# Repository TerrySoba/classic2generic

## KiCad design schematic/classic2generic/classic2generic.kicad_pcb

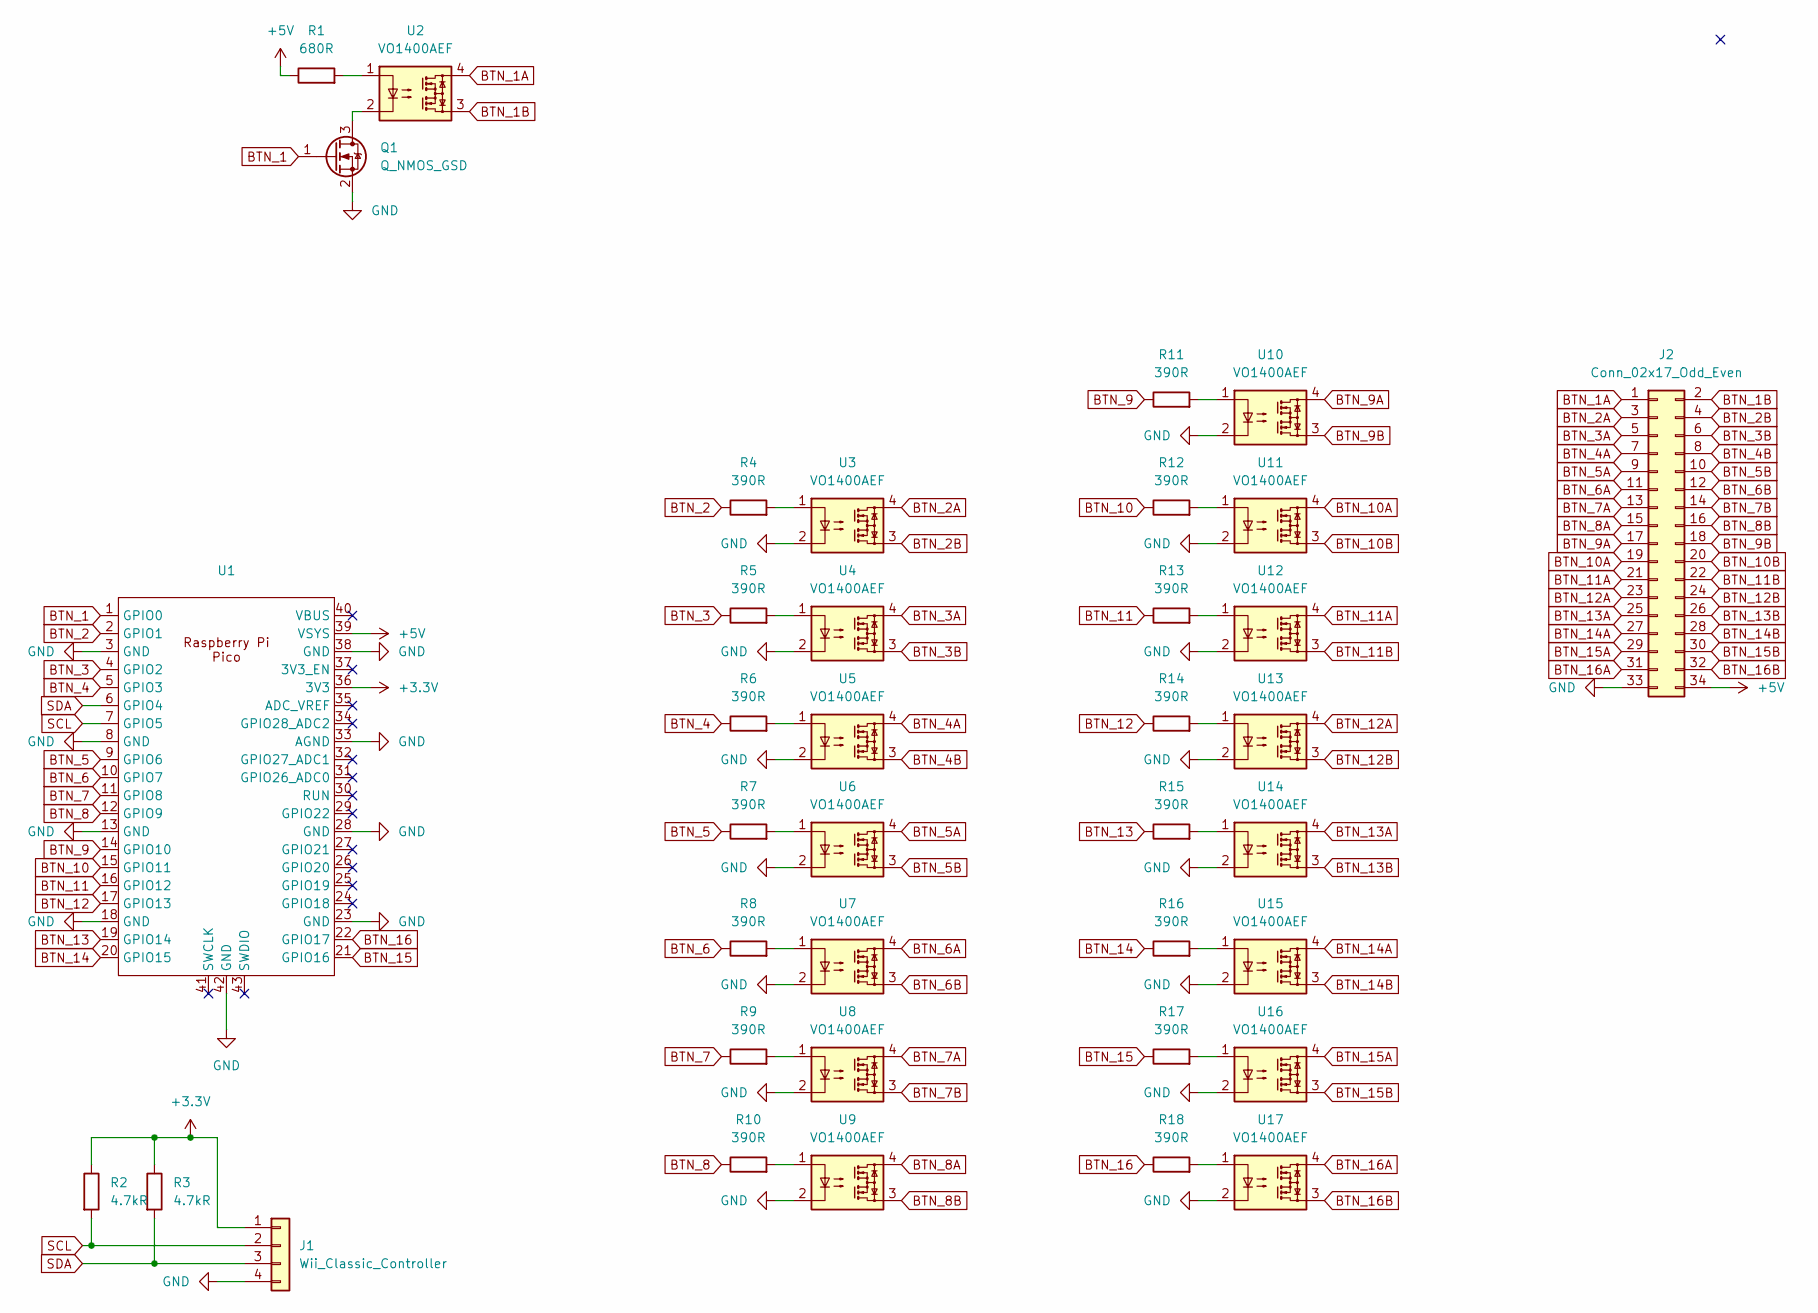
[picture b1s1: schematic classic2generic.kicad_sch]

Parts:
J1: Wii_Classic_Controller; Molex_KK-254_AE-6410-04A_1x04_P2.54mm_Vertical
J2: Conn_02x17_Odd_Even; IDC-Header_2x17_P2.54mm_Vertical
Q1: Q_NMOS_GSD
R1: 680R; R_0603_1608Metric_Pad0.98x0.95mm_HandSolder
R2, R3: 4.7kR; R_0805_2012Metric_Pad1.20x1.40mm_HandSolder
R4, R5, R6, R7, R8, R9, R10, R11, R12, R13, R14, R15, R16, R17, R18: 390R; R_0603_1608Metric_Pad0.98x0.95mm_HandSolder
U1: RPi_Pico_SMD_TH
U2, U3, U4, U5, U6, U7, U8, U9, U10, U11, U12, U13, U14, U15, U16, U17: VO1400AEF; SO-4_4.4x4.3mm_P2.54mm

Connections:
+3.3V: J1.1, R2.1, R3.1, U1.36 (3V3)
BTN_1A: J2.1, U2.4
BTN_1B: J2.2, U2.3
BTN_2: R4.1, U1.2 (GPIO1)
BTN_2A: J2.3, U3.4
BTN_2B: J2.4, U3.3
BTN_3: R5.1, U1.4 (GPIO2)
BTN_3A: J2.5, U4.4
BTN_3B: J2.6, U4.3
BTN_4: R6.1, U1.5 (GPIO3)
BTN_4A: J2.7, U5.4
BTN_4B: J2.8, U5.3
BTN_5: R7.1, U1.9 (GPIO6)
BTN_5A: J2.9, U6.4
BTN_5B: J2.10, U6.3
BTN_6: R8.1, U1.10 (GPIO7)
BTN_6A: J2.11, U7.4
BTN_6B: J2.12, U7.3
BTN_7: R9.1, U1.11 (GPIO8)
BTN_7A: J2.13, U8.4
BTN_7B: J2.14, U8.3
BTN_8: R10.1, U1.12 (GPIO9)
BTN_8A: J2.15, U9.4
BTN_8B: J2.16, U9.3
BTN_9: R11.1, U1.14 (GPIO10)
BTN_9A: J2.17, U10.4
BTN_9B: J2.18, U10.3
BTN_10: R12.1, U1.15 (GPIO11)
BTN_10A: J2.19, U11.4
BTN_10B: J2.20, U11.3
BTN_11: R13.1, U1.16 (GPIO12)
BTN_11A: J2.21, U12.4
BTN_11B: J2.22, U12.3
BTN_12: R14.1, U1.17 (GPIO13)
BTN_12A: J2.23, U13.4
BTN_12B: J2.24, U13.3
BTN_13: R15.1, U1.19 (GPIO14)
BTN_13A: J2.25, U14.4
BTN_13B: J2.26, U14.3
BTN_14: R16.1, U1.20 (GPIO15)
BTN_14A: J2.27, U15.4
BTN_14B: J2.28, U15.3
BTN_15: R17.1, U1.21 (GPIO16)
BTN_15A: J2.29, U16.4
BTN_15B: J2.30, U16.3
BTN_16: R18.1, U1.22 (GPIO17)
BTN_16A: J2.31, U17.4
BTN_16B: J2.32, U17.3
GND: J1.4, J2.33, Q1.2 (S), Q1.3 (D), U1.3 (GND), U1.8 (GND), U1.13 (GND), U1.18 (GND), U1.23 (GND), U1.28 (GND), U1.33 (AGND), U1.38 (GND), U1.42 (GND), U2.2, U3.2, U4.2, U5.2, U6.2, U7.2, U8.2, U9.2, U10.2, U11.2, U12.2, U13.2, U14.2, U15.2, U16.2, U17.2
unnamed: R1.2, U2.1
unnamed: R4.2, U3.1
unnamed: R5.2, U4.1
unnamed: R6.2, U5.1
unnamed: R7.2, U6.1
unnamed: R8.2, U7.1
unnamed: R9.2, U8.1
unnamed: R10.2, U9.1
unnamed: R11.2, U10.1
unnamed: R12.2, U11.1
unnamed: R13.2, U12.1
unnamed: R14.2, U13.1
unnamed: R15.2, U14.1
unnamed: R16.2, U15.1
unnamed: R17.2, U16.1
unnamed: R18.2, U17.1
SCL: J1.2, R2.2, U1.7 (GPIO5)
SDA: J1.3, R3.2, U1.6 (GPIO4)

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
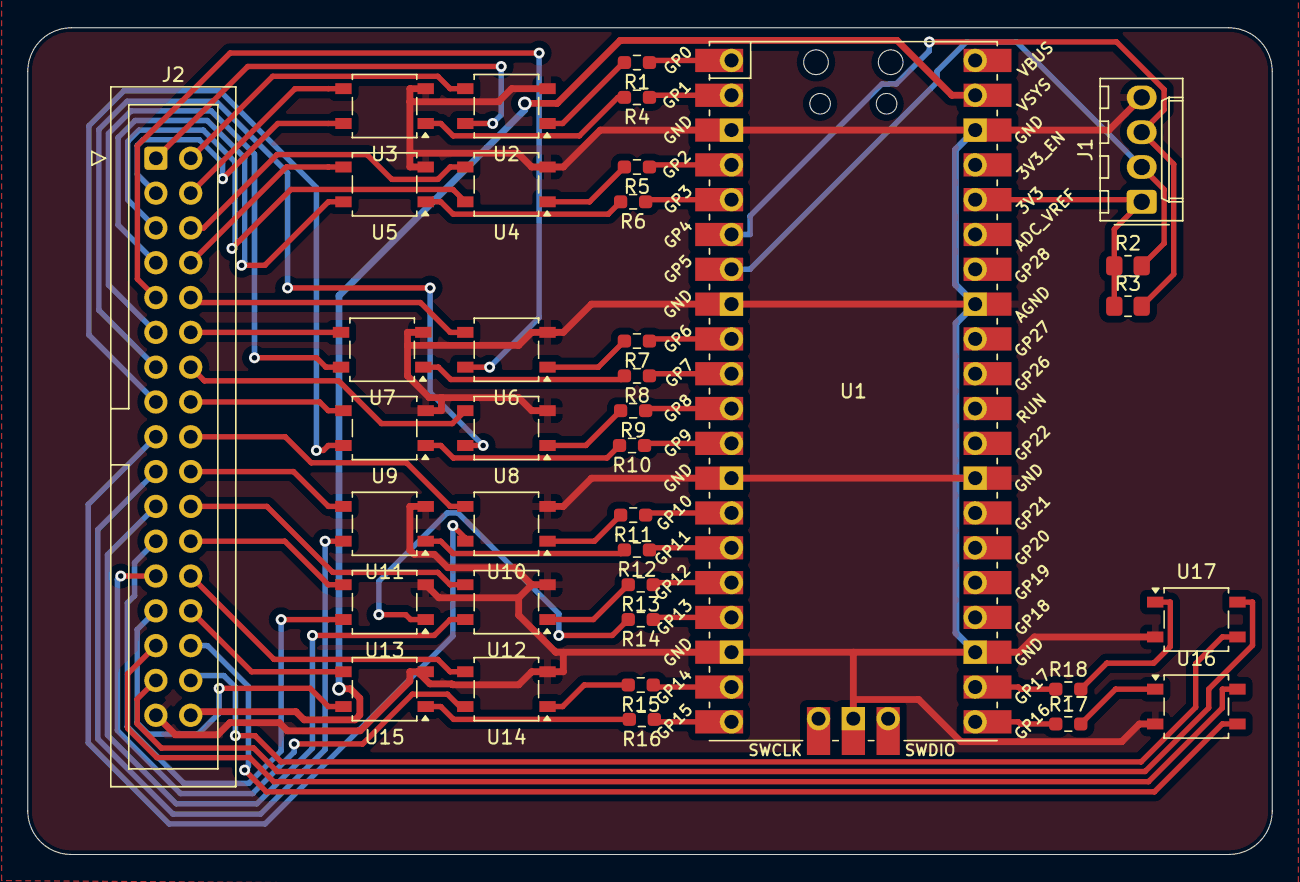
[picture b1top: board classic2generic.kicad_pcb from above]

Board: 2 copper layers, 90.8 x 60.3 mm, 37 parts (0 on the bottom side), 69 nets.

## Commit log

2024-11-25 Initial import
